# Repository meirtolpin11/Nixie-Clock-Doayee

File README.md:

# Nixie Clock Driver (Doayee IN-12B)

A 6-digit IN-12B Nixie tube display and driver board designed in KiCad.

---

## Overview

This project is a modular Nixie tube driver board tailored for Russian **IN-12B** cold-cathode neon display tubes. It utilizes the **HV5122PG** high-voltage 32-channel shift register IC to drive tube cathodes with minimal microcontroller I/O pins, paired with individually driven RGB backlights underneath each tube.

### Key Features
* **6x IN-12B Nixie Tube Sockets**: DSUB-style footprint mounting with decimal point support.
* **Microchip/Supertex HV5122PG High-Voltage Driver**: 32 high-voltage open-drain outputs with internal shift register and latch.
* **RGB Tube Backlighting**: Dedicated Cree PLCC4 / SMD RGB LEDs for under-glow effects.
* **Integrated Logic**: 74LVC1G79 D-type flip-flop for high-speed clock/data synchronization.
* **Self-Contained Library Management**: All custom symbols, footprints, and 3D models are bundled in the repository and mapped via relative project variables (`${KIPRJMOD}`).

---

## Repository Structure

```
├── Nixie.kicad_pro              # KiCad project file
├── Nixie.kicad_sch              # Main schematic
├── Nixie.kicad_pcb              # PCB layout
├── sym-lib-table                # Project symbol library table (portable ${KIPRJMOD})
├── fp-lib-table                 # Project footprint library table (portable ${KIPRJMOD})
├── libs/                        # Bundled component libraries
│   ├── symbols/                 # Symbol libraries (.kicad_sym)
│   │   ├── HV5122_Doayee.kicad_sym
│   │   ├── HV5122PG-G.kicad_sym
│   │   ├── 74LVC1G79GW-Q100H.kicad_sym
│   │   ├── nixies-us.kicad_sym
│   │   ├── mynixies.kicad_sym
│   │   ├── nixiemisc.kicad_sym
│   │   └── CustomComponents.kicad_sym
│   ├── footprints/              # Footprint libraries (.pretty folders)
│   │   ├── HV5122PG-G.pretty/
│   │   ├── 74LVC1G79GW.pretty/
│   │   ├── nixies-us.pretty/
│   │   ├── mynixies.pretty/
│   │   ├── nixiemisc.pretty/
│   │   └── CustomComponents.pretty/
│   └── 3dmodels/                # 3D models (.wrl / .step)
│       └── IN-12B.wrl, box_header_*.wrl
├── datasheets/                  # Component datasheets (IN-12B, HV5122, etc.)
├── production/                  # Manufacturing outputs
│   └── gerbers/                 # Gerbers and drill files
├── docs/                        # Exported documentation
│   ├── schematic.pdf            # Schematic in PDF format
│   └── pcb_top.svg              # Top-layer SVG rendering
└── archive/                     # Historical KiCad 4/5 files
    └── legacy_kicad4/
```

---

## How to Open in KiCad

1. Clone this repository:
   ```bash
   git clone git@github.com:meirtolpin11/Nixie-Clock-Doayee.git
   ```
2. Open **KiCad** (version 7, 8, 9, or 10).
3. Select **File -> Open Project...** and select `Nixie.kicad_pro`.
4. All symbols and footprints are pre-configured to resolve automatically using `${KIPRJMOD}`—no manual library configuration is needed.

---

## Documentation & Exports

* **Schematic PDF**: [docs/schematic.pdf](docs/schematic.pdf)
* **Gerber Files**: [production/gerbers/](production/gerbers/)
* **Datasheets**: [datasheets/](datasheets/)

---

## License

Hardware design and files are provided for personal and open-source hobbyist use.

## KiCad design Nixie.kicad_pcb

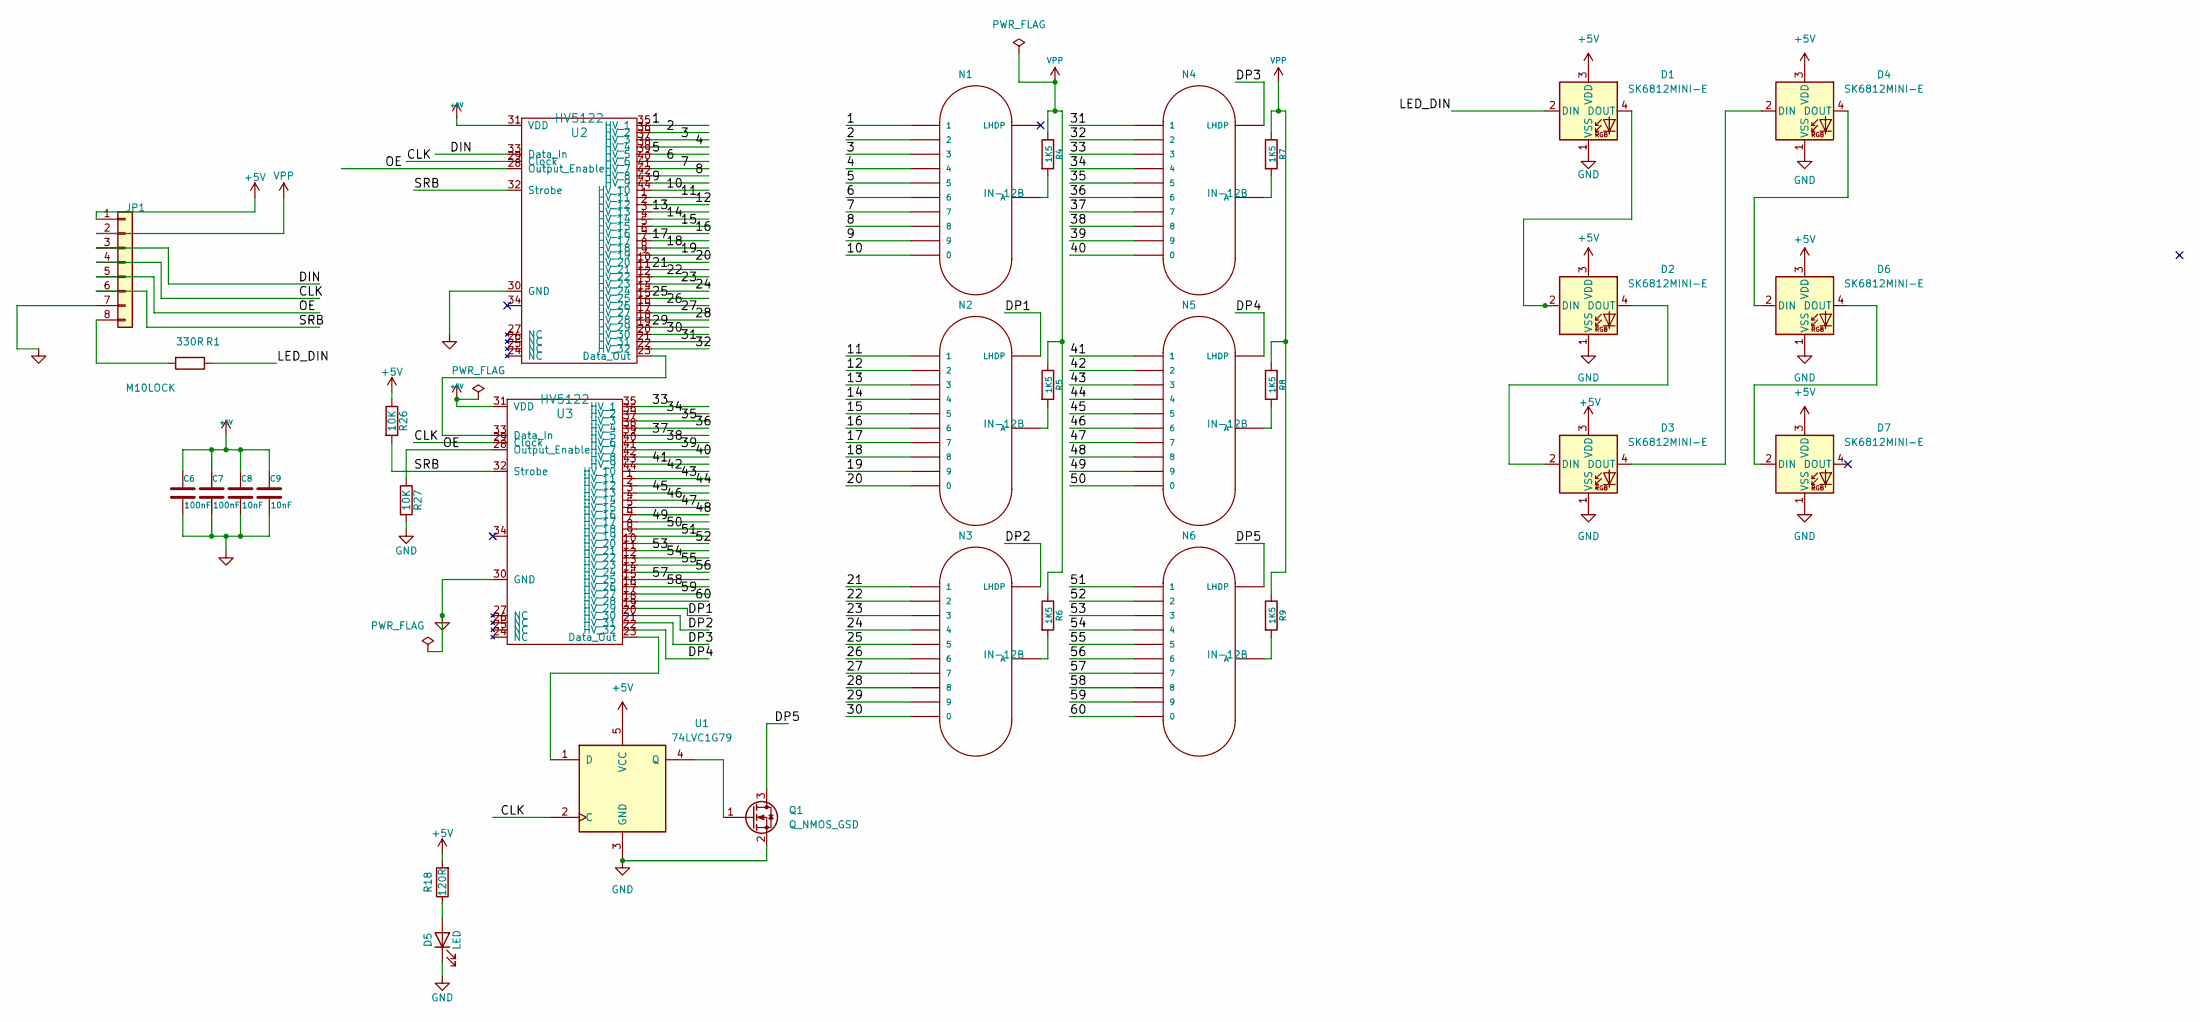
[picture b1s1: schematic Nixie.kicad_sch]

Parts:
C6, C7: 100nF; C_Disc_D4.7mm_W2.5mm_P5.00mm
C8, C9: 10nF; C_Disc_D4.7mm_W2.5mm_P5.00mm
D1, D2, D3, D4, D6, D7: SK6812MINI-E; LED_SK6812MINI-E_3.2x2.8mm_P1.5mm_ReverseMount
D5: LED; LED_D3.0mm
JP1: M10LOCK; PinHeader_1x08_P2.54mm_Vertical
N1, N2, N3, N4, N5, N6: IN-12B; nixies-us-IN-12-DSUB-NOHOLE
Q1: Q_NMOS_GSD; SOT-23
R1: 330R; R_Axial_DIN0207_L6.3mm_D2.5mm_P7.62mm_Horizontal
R4, R5, R6, R7, R8, R9: 1K5; R_Axial_DIN0207_L6.3mm_D2.5mm_P7.62mm_Horizontal
R18: 120R; R_Axial_DIN0207_L6.3mm_D2.5mm_P7.62mm_Horizontal
R26, R27: 10K; R_Axial_DIN0207_L6.3mm_D2.5mm_P7.62mm_Horizontal
U1: 74LVC1G79; SOT-23-5_HandSoldering
U2, U3: HV5122; QFP80P1390X1390X235-44N

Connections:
+5V: C6.1, C7.1, C8.1, C9.1, D1.3 (VDD), D2.3 (VDD), D3.3 (VDD), D4.3 (VDD), D6.3 (VDD), D7.3 (VDD), JP1.1, R18.2, R26.1, U1.5 (VCC), U2.31 (VDD), U3.31 (VDD)
/1: N1.1, U2.35 (HV_1)
/2: N1.2, U2.36 (HV_2)
/3: N1.3, U2.37 (HV_3)
/4: N1.4, U2.38 (HV_4)
/5: N1.5, U2.39 (HV_5)
/6: N1.6, U2.40 (HV_6)
/7: N1.7, U2.41 (HV_7)
/8: N1.8, U2.42 (HV_8)
/9: N1.9, U2.43 (HV_9)
/10: N1.0, U2.44 (HV_10)
/11: N2.1, U2.1 (HV_11)
/12: N2.2, U2.2 (HV_12)
/13: N2.3, U2.3 (HV_13)
/14: N2.4, U2.4 (HV_14)
/15: N2.5, U2.5 (HV_15)
/16: N2.6, U2.6 (HV_16)
/17: N2.7, U2.7 (HV_17)
/18: N2.8, U2.8 (HV_18)
/19: N2.9, U2.9 (HV_19)
/20: N2.0, U2.10 (HV_20)
/21: N3.1, U2.11 (HV_21)
/22: N3.2, U2.12 (HV_22)
/23: N3.3, U2.13 (HV_23)
/24: N3.4, U2.14 (HV_24)
/25: N3.5, U2.15 (HV_25)
/26: N3.6, U2.16 (HV_26)
/27: N3.7, U2.17 (HV_27)
/28: N3.8, U2.18 (HV_28)
/29: N3.9, U2.19 (HV_29)
/30: N3.0, U2.20 (HV_30)
/31: N4.1, U2.21 (HV_31)
/32: N4.2, U2.22 (HV_32)
/33: N4.3, U3.35 (HV_1)
/34: N4.4, U3.36 (HV_2)
/35: N4.5, U3.37 (HV_3)
/36: N4.6, U3.38 (HV_4)
/37: N4.7, U3.39 (HV_5)
/38: N4.8, U3.40 (HV_6)
/39: N4.9, U3.41 (HV_7)
/40: N4.0, U3.42 (HV_8)
/41: N5.1, U3.43 (HV_9)
/42: N5.2, U3.44 (HV_10)
/43: N5.3, U3.1 (HV_11)
/44: N5.4, U3.2 (HV_12)
/45: N5.5, U3.3 (HV_13)
/46: N5.6, U3.4 (HV_14)
/47: N5.7, U3.5 (HV_15)
/48: N5.8, U3.6 (HV_16)
/49: N5.9, U3.7 (HV_17)
/50: N5.0, U3.8 (HV_18)
/51: N6.1, U3.9 (HV_19)
/52: N6.2, U3.10 (HV_20)
/53: N6.3, U3.11 (HV_21)
/54: N6.4, U3.12 (HV_22)
/55: N6.5, U3.13 (HV_23)
/56: N6.6, U3.14 (HV_24)
/57: N6.7, U3.15 (HV_25)
/58: N6.8, U3.16 (HV_26)
/59: N6.9, U3.17 (HV_27)
/60: N6.0, U3.18 (HV_28)
/CLK: JP1.4, U1.2 (C), U2.29 (Clock), U3.29 (Clock)
/DIN: JP1.3, U2.33 (Data_In)
/DP1: N2.LHDP, U3.19 (HV_29)
/DP2: N3.LHDP, U3.20 (HV_30)
/DP3: N4.LHDP, U3.21 (HV_31)
/DP4: N5.LHDP, U3.22 (HV_32)
/DP5: N6.LHDP, Q1.3 (D)
/LED_DIN: D1.2 (DIN), R1.1
/OE: JP1.5, R27.1, U2.28 (Output_Enable), U3.28 (Output_Enable)
/SRB: JP1.6, R26.2, U2.32 (Strobe), U3.32 (Strobe)
GND: C6.2, C7.2, C8.2, C9.2, D1.1 (VSS), D2.1 (VSS), D3.1 (VSS), D4.1 (VSS), D5.1 (K), D6.1 (VSS), D7.1 (VSS), JP1.7, Q1.2 (S), R27.2, U1.3 (GND), U2.30 (GND), U3.30 (GND)
unnamed: D1.4 (DOUT), D2.2 (DIN)
unnamed: D2.4 (DOUT), D3.2 (DIN)
unnamed: D3.4 (DOUT), D4.2 (DIN)
unnamed: D4.4 (DOUT), D6.2 (DIN)
unnamed: D5.2 (A), R18.1
unnamed: D6.4 (DOUT), D7.2 (DIN)
unnamed: JP1.8, R1.2
unnamed: N1.A, R4.2
unnamed: N2.A, R5.2
unnamed: N3.A, R6.2
unnamed: N4.A, R7.2
unnamed: N5.A, R8.2
unnamed: N6.A, R9.2
unnamed: Q1.1 (G), U1.4 (Q)
unnamed: U1.1 (D), U3.23 (Data_Out)
unnamed: U2.23 (Data_Out), U3.33 (Data_In)
VPP: JP1.2, R4.1, R5.1, R6.1, R7.1, R8.1, R9.1

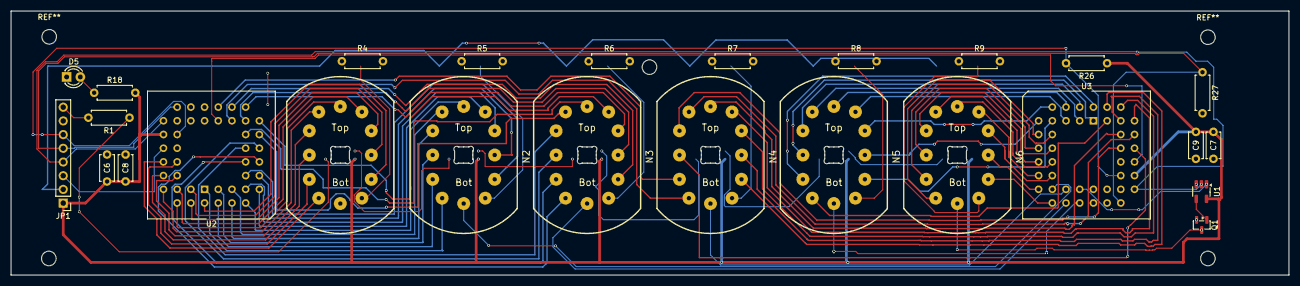
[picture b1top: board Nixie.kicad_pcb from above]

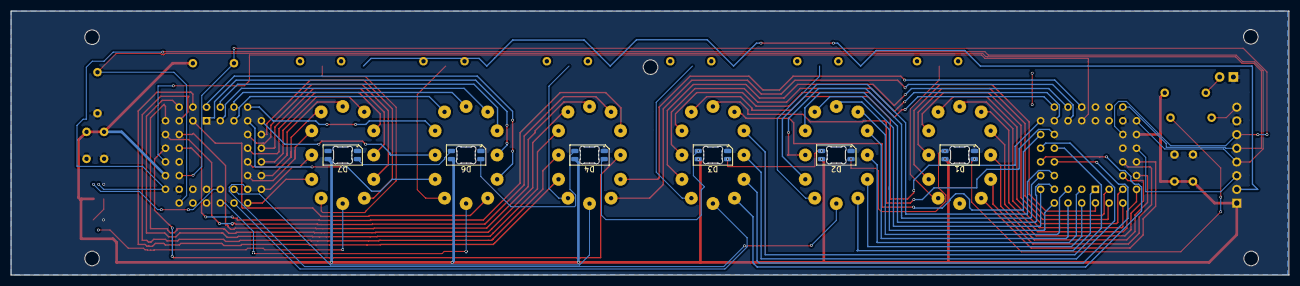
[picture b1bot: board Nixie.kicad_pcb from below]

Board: 2 copper layers, 237.0 x 48.9 mm, 32 parts (6 on the bottom side), 89 nets.
